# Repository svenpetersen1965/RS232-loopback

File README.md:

# RS232-loopback
This is a loopback module for the serial interface (RS232 and TTL).

It is useful for testing a serial interface. The sent data is echoed back, the RTS is fed back to CTS and DTR is looped back to DSR, DCD and RI. The feedbacks can be jumpered, the status is indicated on LEDs and it connects to DTE and DCE (9 pin D-Sub connectors). Also, there is a box connector for connecting a ribbon cable.

Please refer to the documentation in the pdf subdirectory.

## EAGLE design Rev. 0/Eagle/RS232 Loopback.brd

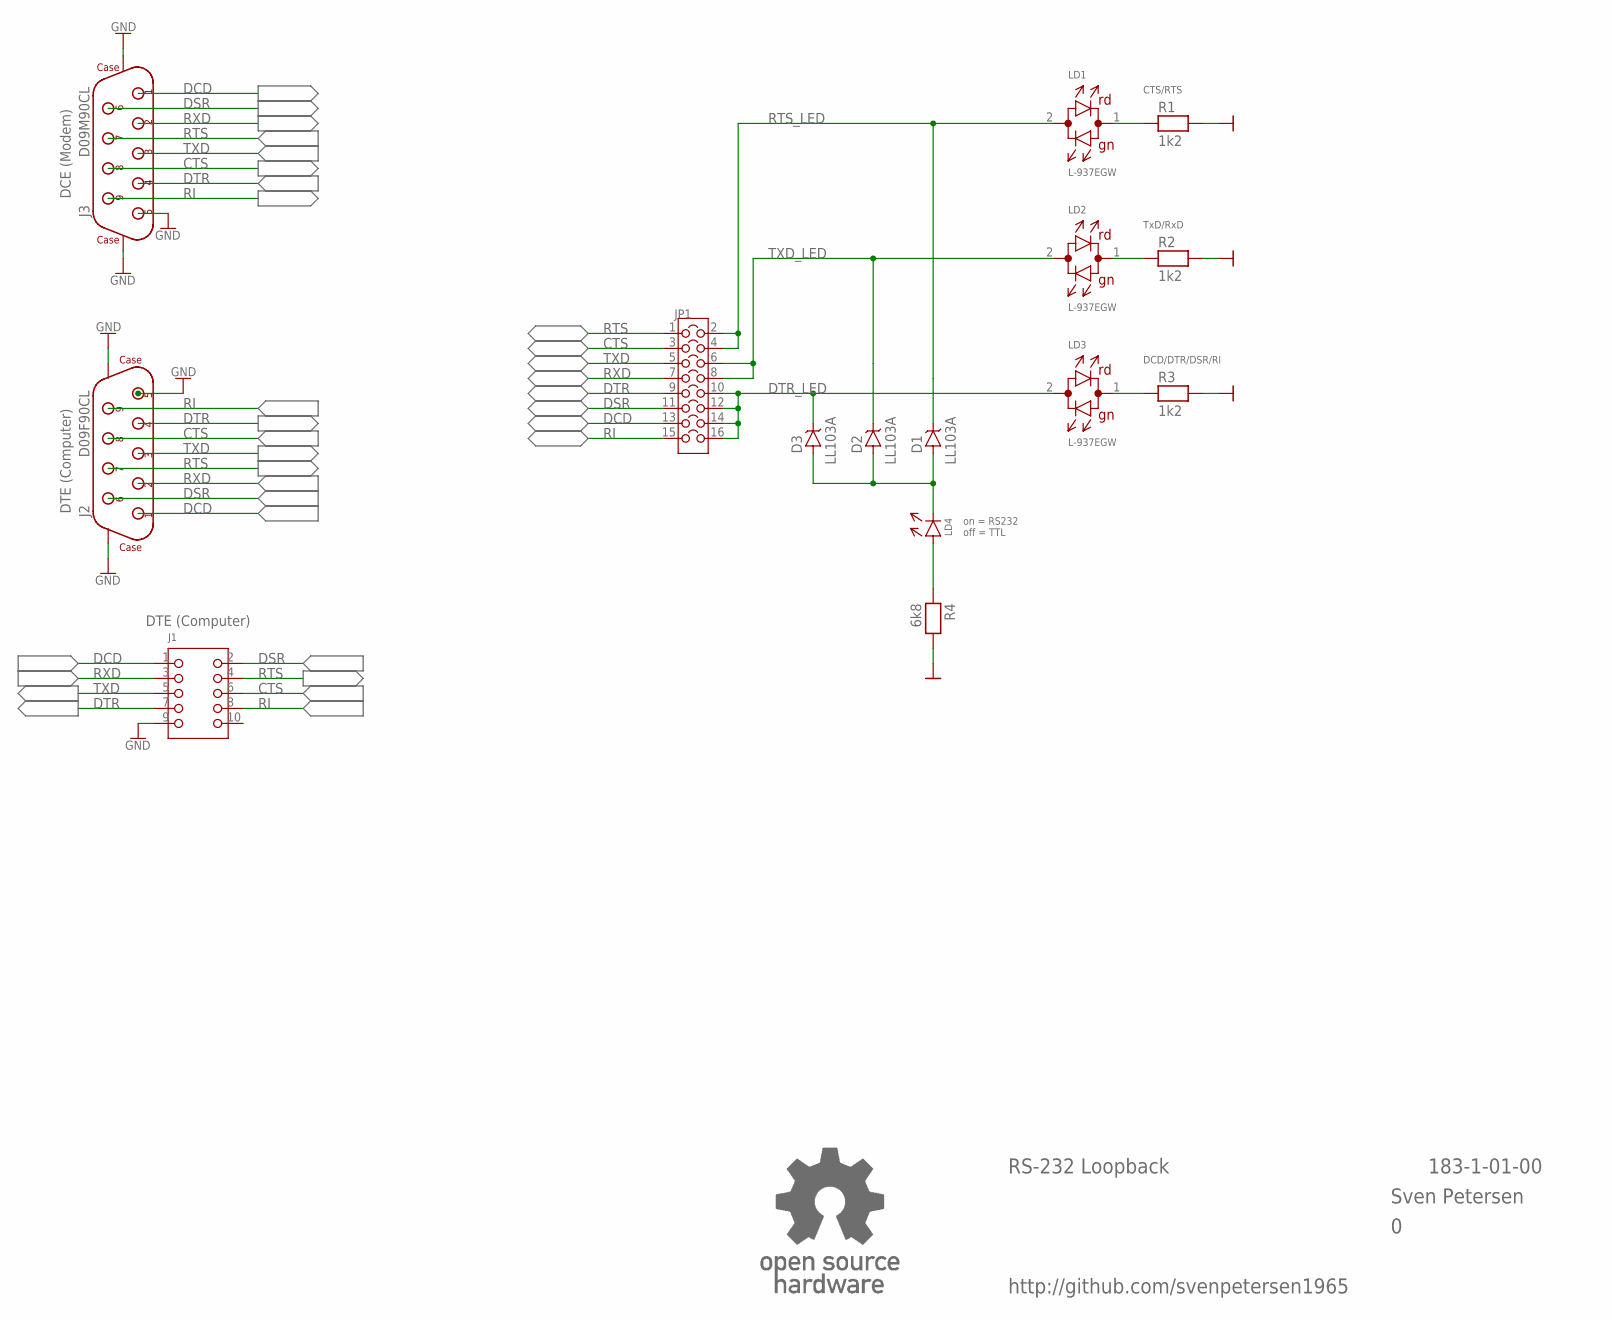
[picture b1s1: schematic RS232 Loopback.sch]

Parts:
D1, D2, D3: LL103A; SOD80C
J1: 2X05WV
J2: D09F90CL
J3: D09M90CL
JP1: COMBI-8X2P; COMBI-8X2
LD1, LD2, LD3: L-937EGW; LED_3MM_BICOLOR
LD4: 3MM
R1, R2, R3: 1k2; 0805
R4: 6k8; 0805
U$44: OPEN_SOURCE_HW; OPENHW

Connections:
CTS: J1.6, J2.8, J3.8, JP1.3
DCD: J1.1, J2.1, J3.1, JP1.13
DSR: J1.2, J2.6, J3.6, JP1.11
DTR: J1.7, J2.4, J3.4, JP1.9
DTR_LED: D3.K, JP1.10, JP1.12, JP1.14, JP1.16, LD3.2
GND: J1.9, J2.5, J2.CL1 (CASE1), J2.CL2 (CASE2), J3.5, J3.CL1 (CASE1), J3.CL2 (CASE2), R1.2, R2.2, R3.2, R4.2
unnamed: D1.A, D2.A, D3.A, LD4.C (K)
unnamed: LD4.A, R4.1
unnamed: LD1.1, R1.1
unnamed: LD2.1, R2.1
unnamed: LD3.1, R3.1
RI: J1.8, J2.9, J3.9, JP1.15
RTS: J1.4, J2.7, J3.7, JP1.1
RTS_LED: D1.K, JP1.2, JP1.4, LD1.2
RXD: J1.3, J2.2, J3.2, JP1.7
TXD: J1.5, J2.3, J3.3, JP1.5
TXD_LED: D2.K, JP1.6, JP1.8, LD2.2

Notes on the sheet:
CTS/RTS
TxD/RxD
on = RS232 off = TTL
DCD/DTR/DSR/RI
DTE (Computer)
DCE (Modem)
http://github.com/svenpetersen1965
Sven Petersen
RS-232 Loopback
183-1-01-00

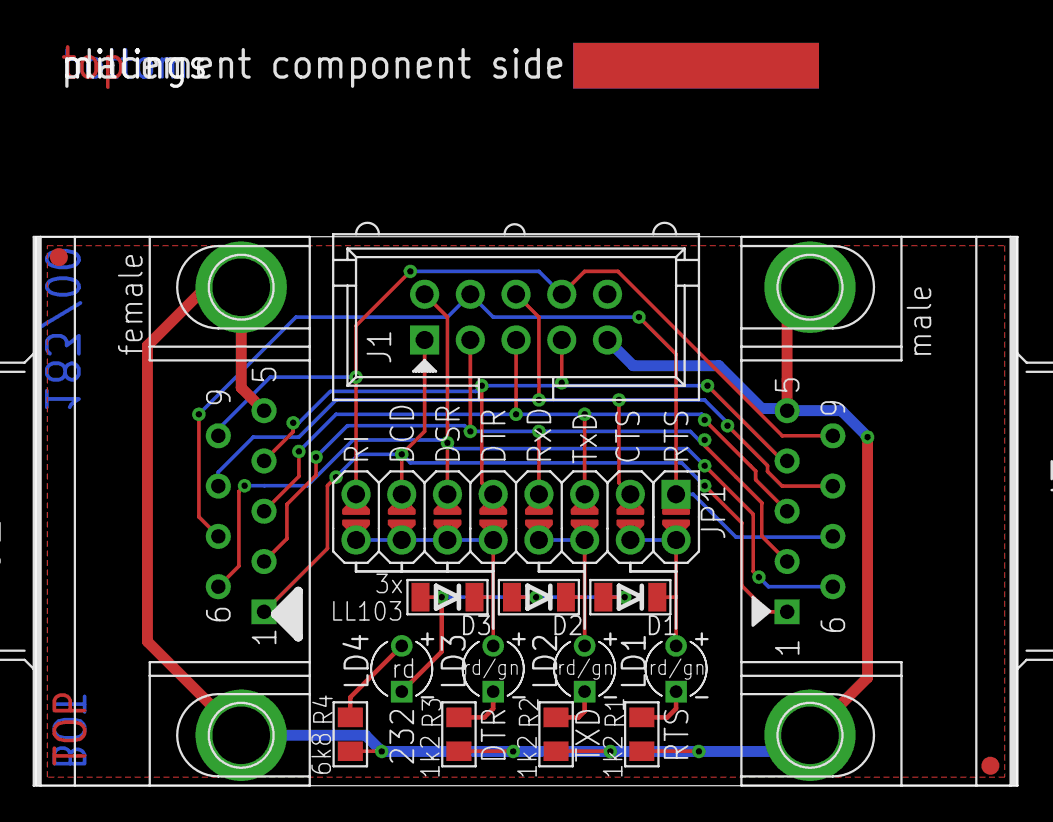
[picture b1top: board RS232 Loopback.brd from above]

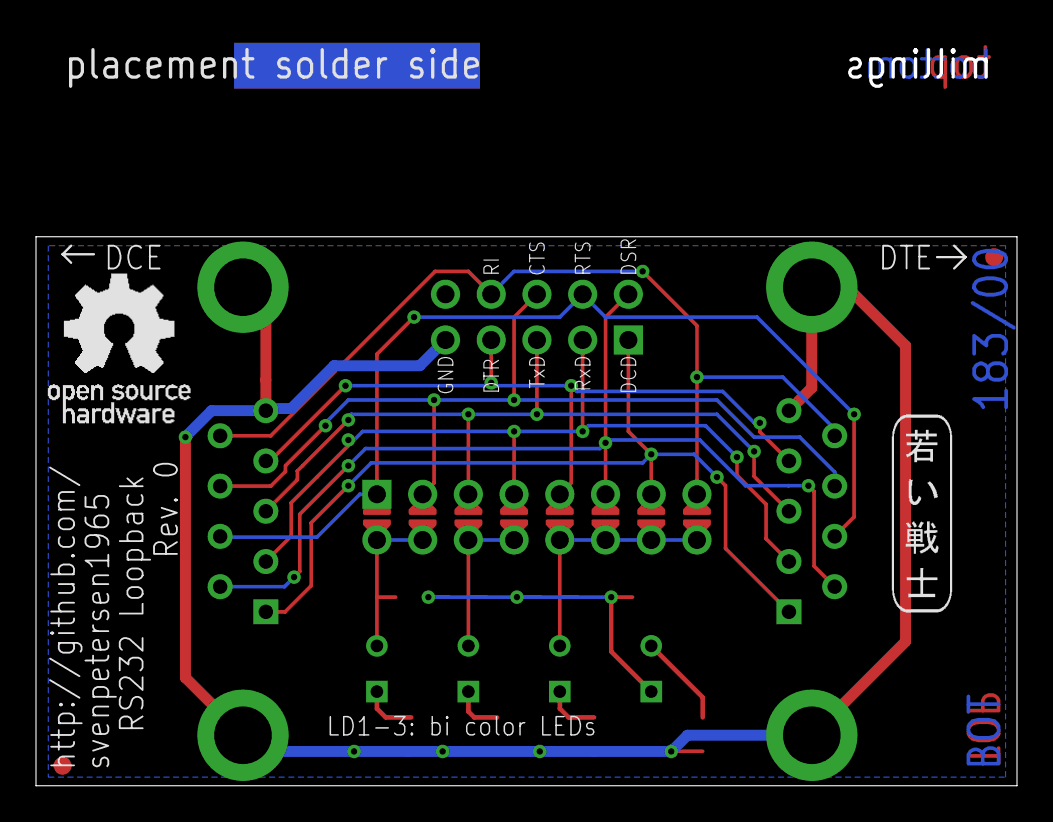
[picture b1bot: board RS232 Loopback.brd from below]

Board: 2 copper layers, 54.5 x 41.7 mm, 21 parts (2 on the bottom side), 17 nets.

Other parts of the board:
U$2: 2LAYER
U$3, U$43: SMD_REF_R1MM
U$45: PCB-TITLE/
U$46: SVEN_TAG

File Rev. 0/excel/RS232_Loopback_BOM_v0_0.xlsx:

RS-232 Loopback Rev. 0
Bill of Material Rev. 0.0
Pos. | Qty | Value | Footprint | Ref.-No. | Comment
1 | 1 | 183-2-01-00 | 2 Layer | PCB Rev. 0 | 2 layer, Cu 35µ, HASL, 54.5mm x 30.5mm, 1.6mm FR4
2 | 1 | box header, 2x5, 2.54mm | 2X05WV | J1 | e.g. Reichelt WSL 10G
3 | 1 | LED, 3mm green | 3MM | LD4 | standard LED
4 | 3 | 1k2 | 805 | R1, R2, R3 | SMD metal film resistor, 5% or better
5 | 1 | 6k8 | 805 | R4 | SMD metal film resistor, 5% or better
6 | 1 | COMBI-8X2P | COMBI-8X2 | JP1 | solder bridges or 2x8 pin header
7 | 8 | Jumper, 2.54mm | jumper | (JP1) | standard jumper (rated 1A or more). E.G. Reichelt: JUMPER 2,54 SW, tme.eu: 6342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
8 | 1 | D09F90CL | D09F90CL | J2 | DSUB, 9p, female, 90°. E.g. Reichelt D-SUB BU 09EU
9 | 1 | D09M90CL | D09M90CL | J3 | DSUB, 9p, male, 90°. E.g. Reichelt D-SUB ST 09EU
10 | 3 | L-937EGW | LED_3MM_BICOLOR | LD1, LD2, LD3 | bi-color 3mm LED (green, red), e.g. Kingbright, e.g. Reichelt LED 3 RG
11 | 3 | LL103A | SOD-80 | D1, D2, D3 | SMD schottky diode, e.g. Vishay

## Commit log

2022-04-27 Initial release
